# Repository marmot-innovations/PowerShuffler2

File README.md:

# PowerShuffler2
Summary: PowerShuffler2 is an update and modification of PowerShuffler1 to handle dual battery charging by intelligently multiplexing between two outputs.

Theory of operation: In a battery stack with 99 lithium-ion cells in series, there might be more than 1 weak cells that limit the usability of the entire battery pack. Let's assume the 99 li-ion cells are arranged in groups of 9 and there are certain groups that contain cells which are stronger than others. PowerShuffler2 is a PCBA that will piggy-back on top of the existing BMS that comes with the battery pack and draw power from the stronger group in order to charge up the 1 or 2 weak cells wherever they sit in the series of 99 cells. PowerShuffler2 has built-in intelligence to select the lower of the two output cell voltages and to prevent over-discharging the stronger group by measuring the voltage of the weakest cell as it rises, and comparing it to 1/9th of the stronger group's total voltage as it falls to within a certain threshold. Pre-programmed hysteresis and voltage-read-before-charging prevents excessive start-stop charging as the cells are put through normal usage during the time when the existing BMS kicks in. Although intrusive, PowerShuffler2 is meant to be a diagnostics tool to verify and characterize weak cells within a battery stack on top of a pre-existing BMS. It does not replace the need for servicing the battery pack or using a better BMS down the road. PowerShuffler2 has no wired or wireless communication, which is not accessible anyway if piggy-backed within a battery pack enclosure.

Included in this project are:
1. Firmware for client MCU
2. PCB design for PCBA

Not included in this project is:
1. Firmware for master MCU (see PowerShuffler1 project)

Read the individual README for further details. Pictures will be added later to provide instructions for programming and installation, as well as board modifications where needed. Test data will be provided eventually.

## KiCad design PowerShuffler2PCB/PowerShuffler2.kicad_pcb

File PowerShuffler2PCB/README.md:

## PowerShuffler 2.0 PCB design schematic, layout, Gerbers, and BOM  
KiCAD 5.0.0 for PCB design  
Microsoft Excel web for BOM  
No 3D model  
No XY pick and place Centroid  
No ODB++  
No footprint library  
No schematic library

Design bugs and comments:  
1. To program master MCU, remove R6 and C7 first, then replace them once programming is completed. These components will put too much load on ISP TPI programmer.
2. To program client MCU, remove C24 and R22 first, then replace them once completed. These components will put too much load on ISP TPI programmer.
3. J2 and J4 do not need soldered headers for programming. Just shove a 5-pin 0.1" straight strip header into it to establish electrical contact. Look up "sneaky footprints PCB" on the web.
4. Mounting holes are for 4-40 screws and stand-offs.
5. Peak 82% efficiency during max charge rate as measured.
6. Less than 0.5mA current draw from input when idle, not charging.
7. There is no D2 LED, only D1 and D3.

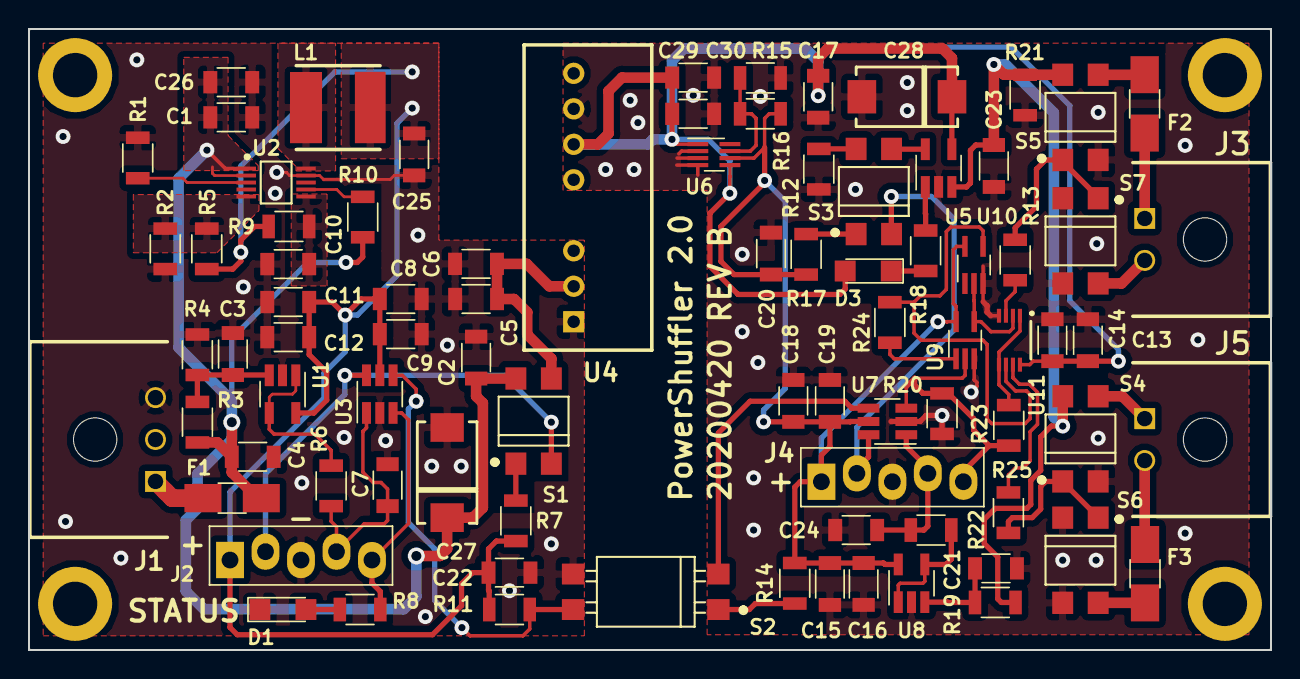
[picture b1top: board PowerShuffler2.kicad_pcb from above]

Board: 4 copper layers, 88.9 x 44.5 mm, 88 parts (0 on the bottom side), 49 nets.

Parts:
C1, C3, C5, C7, C8, C11, C13, C15, C18, C21, C22, C24, C29: 1u; C_1206
C2, C6, C9, C12, C14, C16, C19, C26, C30: 0.1u; C_1206
C4, C20, C25: 10u; C_1206
C10: 0.22u; C_1206
C17, C23: 4.7u; C_1206
C27, C28: 15u; 2917
D1, D3: LED; LED_1206
F1, F2, F3: Fuse; Fuse_SMD1206_HandSoldering
J1: Conn_01x03; Molex_Microfit3_Header_3pin_Angled_43650
J2, J4: Conn_01x05; Staggered_ICSP_5x2.54mm_Straight
J3, J5: Conn_01x02; Molex_Microfit3_Header_2pin_Angled_43650
L1: 680u; SMD_Inductor_Shielded_6x6mm
MNT1, MNT2, MNT3, MNT4: MountingHole; 3mm_hole
R1, R10, R21, R24: 191k; R_1206
R2: 49.9k; R_1206
R3: 210k; R_1206
R4: 19.1k; R_1206
R5: 158k; R_1206
R6, R13, R19, R22, R25: 390; R_1206
R7: 470; R_1206
R8, R11, R12, R18: 2k; R_1206
R9: 22.1; R_1206
R14, R17: 820; R_1206
R15: 200k; R_1206
R16, R23: 1.33M; R_1206
R20: 5.6k; R_1206
S1, S3, S4, S5, S6, S7: SSR4; SMD4_SSR_CPC1002N
S2: OPTOSOLO; SMD4_TL241AF-SSR_0.1_12x5mm
U1, U8: MCP6401; SOT-23-5_HandSoldering
U2: SWITCHDCDCLOPOW; 10-μMAX_3x3mm
U3, U7: ATTINY; SOT-23-6_Handsoldering
U4: SPBW03G
U5: MCP73831; SOT-23-5_HandSoldering
U6: LT3009; SC-70-8_Handsoldering
U9: 74AUC1G79; SOT-353_SC-70-5_Handsoldering
U10: 74AHC1G14; SOT-353_SC-70-5_Handsoldering
U11: SN74LVC2G08; VSSOP-8

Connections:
+3.3VA: C15.1, C16.1, C18.1, C19.1, C20.1, J4.1, R14.1, R16.1, R17.1, U6.6, U7.5, U8.5, U9.5, U10.5
+3V3: C8.1, C9.1, C11.1, C12.1, C22.1, C25.1, J2.1, L1.2, R5.1, R7.2, R9.1, R11.1, U1.5, U3.5
+5VA: C13.1, C14.1, C17.1, C28.1, C29.1, C30.1, D3.2, U4.6, U5.4, U6.1, U6.5, U11.8
+36V: C1.1, C2.1, C4.1, C26.1, C27.1, F1.1, R3.1, R10.2, S1.4, U2.1, U2.2
/36VSWITCH: C5.1, C6.1, S1.3, U4.2
/OUT1: R13.1, U11.3
/OUT2: R25.1, U11.7
/PB0_1: C7.1, J2.4, R6.1, U3.1
/PB0_2: C24.1, J4.4, R22.2, U7.1
/PB1_1: J2.5, R8.1, U3.3
/PB1_2: J4.5, R20.1, R23.2, U7.3, U9.2
/PB2_1: R11.2, S2.4, U3.4
/PB2_2: S2.2, U7.4
/PB3_1: J2.2, S1.2, U3.6
/PB3_2: J4.2, S3.2, U7.6
/VBATT: C23.1, R19.2, R21.1, S4.4, S5.4, U5.3
/VSUBSHEET: C3.1, R3.2, R4.1, U1.3
GND: C13.2, C14.2, C15.2, C16.2, C17.2, C18.2, C19.2, C20.2, C21.2, C23.2, C24.2, C28.2, C29.2, C30.2, J4.3, R12.1, R15.1, R20.2, R21.2, S4.2, S5.2, S6.2, S6.3, S7.2, S7.3, U4.7, U5.2, U6.2, U6.3, U6.4, U7.2, U8.2, U9.3, U10.3, U11.4
GNDS: C1.2, C2.2, C3.2, C4.2, C5.2, C6.2, C7.2, C8.2, C9.2, C10.2, C11.2, C12.2, C22.2, C25.2, C26.2, C27.2, D1.1, J1.3, J2.3, R1.2, R2.1, R4.2, S2.3, U1.2, U2.9, U3.2, U4.1
unnamed: C10.1, R9.2, U2.6
unnamed: C21.1, R19.1, U8.3
unnamed: D1.2, R8.2
unnamed: D3.1, R18.2
unnamed: F1.2, J1.1
unnamed: F2.1, J3.1
unnamed: F2.2, S5.3
unnamed: F3.1, J5.2
unnamed: F3.2, S6.4
unnamed: J3.2, S7.4
unnamed: J5.1, S4.3
unnamed: L1.1, U2.10
unnamed: R1.1, U2.3
unnamed: R2.2, R5.2, U2.5
unnamed: R6.2, U1.1, U1.4
unnamed: R7.1, S1.1
unnamed: R10.1, U2.7
unnamed: R12.2, S3.4
unnamed: R13.2, S5.1, S7.1
unnamed: R14.2, S2.1
unnamed: R15.2, R16.2, U6.7
unnamed: R17.2, S3.1
unnamed: R18.1, U5.1
unnamed: R22.1, U8.1, U8.4
unnamed: R23.1, U11.1, U11.5
unnamed: R24.1, U10.4, U11.6
unnamed: R24.2, U9.1
unnamed: R25.2, S4.1, S6.1
unnamed: S3.3, U5.5
unnamed: U9.4, U10.2, U11.2

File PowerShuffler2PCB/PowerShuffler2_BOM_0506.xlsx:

ref | quantity | qty x 3 | value | Mouser P/N | Manufacturer P/N | description | footprint
C12, C14, C16, C19, C2, C26, C30, C6, C9 | 9 | 27 | 0.1u | 791-1206B104K101CT | 1206B104K101CT | Unpolarized capacitor | Capacitors_SMD:C_1206
C10 | 1 | 3 | 0.22u |  | CL31B224KBFNNNE | Unpolarized capacitor | Capacitors_SMD:C_1206
R16, R23 | 2 | 6 | 1.33M | 667-ERJ-8ENF1334V | ERJ-8ENF1334V | Resistor 1% | Resistors_SMD:R_1206
C20, C25 | 2 | 6 | 10u | 963-LMK316B7106KL-T | LMK316B7106KL-T | Unpolarized capacitor 10V | Capacitors_SMD:C_1206
C4 | 1 | 3 | 10u |  | CL31B106KBHNNNE | Unpolarized capacitor 50V | Capacitors_SMD:C_1206
R5 | 1 | 3 | 158k |  | RMCF1206FT158K | Resistor 1% | Resistors_SMD:R_1206
C1, C3, C5 | 3 | 9 | 1u |  | CL31B105KCHNNNE | Unpolarized capacitor 100V | Capacitors_SMD:C_1206
C11, C13, C15, C18, C21, C22, C24, C29, C7, C8 | 10 | 30 | 1u | 791-MT31B105K500CT | MT31B105K500CT | Unpolarized capacitor 50V | Capacitors_SMD:C_1206
C17, C23 | 2 | 6 | 4.7u | 80-C1206C475K4P7210 | C1206C475K4PAC7210 | Unpolarized capacitor | Capacitors_SMD:C_1206
C27, C28 | 2 | 6 | 15u | 80-T491X226K50ATAUTO | T491X226K050ATAUTO | Unpolarized capacitor 50V | BMB:2917
R1, R10, R24 | 3 | 9 | 191k | 667-ERJ-8ENF1913V | ERJ-8ENF1913V | Resistor 1% | Resistors_SMD:R_1206
R11, R12, R18, R8 | 4 | 12 | 2k | 652-CR1206FX-2001ELF | CR1206-FX-2001ELF | Resistor 1% | Resistors_SMD:R_1206
R13, R19, R22, R25, R6 | 5 | 15 | 390 | 652-CR1206FX-3900ELF | CR1206-FX-3900ELF | Resistor 1% | Resistors_SMD:R_1206
R14, R17 | 2 | 6 | 820 | 660-RK73B2BTTE821J | RK73B2BTTE821J | Resistor 5% | Resistors_SMD:R_1206
R15 | 1 | 3 | 200k | 667-ERJ-8ENF2003V | ERJ-8ENF2003V | Resistor 1% | Resistors_SMD:R_1206
R3 | 1 | 3 | 210k |  | ERA-8AEB2103V | Resistor 0.1% | Resistors_SMD:R_1206
R4 | 1 | 3 | 18.7k |  | ERA-8AEB1872V | Resistor 0.1% | Resistors_SMD:R_1206
R7 | 1 | 3 | 470 |  | RMCF1206JT470R | Resistor 5% | Resistors_SMD:R_1206
R2 | 1 | 3 | 49.9k |  | RMCF1206FT49K9 | Resistor 1% | Resistors_SMD:R_1206
R20, R21 | 2 | 6 | 5.6k | 652-CR1206FX-5601ELF | CR1206-FX-5601ELF | Resistor 1% | Resistors_SMD:R_1206
R9 | 1 | 3 | 22.1 |  | RMCF1206FT22R1 | Resistor 1% | Resistors_SMD:R_1206
L1 | 1 | 3 | 680u | 810-VLS6045EX-681M | VLS6045EX-681M | Inductor | BMB:SMD_Inductor_Shielded_6x6mm
U1, U8 | 2 | 6 | MCP6401 | 579-MCP6401T-H/OTVAO | MCP6401T-H/OTVAO | Precision Micropower, Low Noise CMOS, Rail-to-Rail Input/Output Operational Amp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 | TO_SOT_Packages_SMD:SOT-23-5_HandSoldering
U10 | 1 | 3 | 74AHC1G14 | 771-74AHC1G14GW-G | 74AHC1G14GW,125 | Single Schmitt NOT Gate, Low-Voltage CMOS | TO_SOT_Packages_SMD:SOT-353_SC-70-5_Handsoldering
U11 | 1 | 3 | SN74LVC2G08 | 595-SN74LVC2G08DCUR | SN74LVC2G08DCUR |  | BMB:VSSOP-8
U2 | 1 | 3 | SWITCHDCDCLOPOW | 700-MAX17550AUB+ | MAX17550AUB+ |  | BMB:10-μMAX_3x3mm
U3, U7 | 2 | 6 | ATTINY | 556-ATTINY10-TSHR | ATTINY10-TSHR |  | TO_SOT_Packages_SMD:SOT-23-6_Handsoldering
U4 | 1 | 3 | SPBW03G | 709-SPBW03G-05 | SPBW03G-05 |  | BMB:SPBW03G
U5 | 1 | 3 | MCP73831 | 579-MCP73831T-3ACIOT | MCP73831T-3ACI/OT | 4.35V Li-Ion 500mA charger SOT-23-5 | TO_SOT_Packages_SMD:SOT-23-5_HandSoldering
U6 | 1 | 3 | LT3009 | 584-LT3009ESC8TRMPBF | LT3009ESC8#TRMPBF |  | TO_SOT_Packages_SMD:SC-70-8_Handsoldering
U9 | 1 | 3 | 74AUC1G79 | 771-74AHC1G79GW-G | 74AHC1G79GW,125 | Single D Flip-Flop, Low-Voltage CMOS | TO_SOT_Packages_SMD:SOT-353_SC-70-5_Handsoldering
J3, J5 | 2 | 6 | Conn_01x02 | 538-43650-0200 | 43650-0200 |  | BMB:Molex_Microfit3_Header_2pin_Angled_43650
J1 | 1 | 3 | Conn_01x03 | 538-43650-0301 | 43650-0301 |  | BMB:Molex_Microfit3_Header_3pin_Angled_43650
J2, J4 | 2 | 6 | Conn_01x05 | N/A | N/A | staggered 0.1" spaced hole programming port | BMB:Staggered_ICSP_5x2.54mm_Straight
F1 | 1 | 3 | Fuse | 576-0468002.NRHF | 0468002.NR | Surface Mount Fuses 1206 SLO-BLO 2A SLIMLINE HALIDE FREE | Fuse_Holders_and_Fuses:Fuse_SMD1206_HandSoldering
F2, F3 | 2 | 6 | Fuse | 650-1206SFP200F/63-2 | 1206SFP200F/63-2 | Surface Mount Fuses VERY FAST GLASS CER 63V 2A SZ 1206 | Fuse_Holders_and_Fuses:Fuse_SMD1206_HandSoldering
D1 | 1 | 3 | LED | 710-150120GS75000 | 150120GS75000 | Green LED 1206 | LEDs:LED_1206
D3 | 1 | 3 | LED | 710-150120RS75000 | 150120RS75000 | Red LED 1206 | LEDs:LED_1206
S1 | 1 | 3 | SSR4 | 849-CPC1002N | CPC1002N | Solid State Relays - PCB Mount 1-Form-A 60V 700mA Solid State Relay MOSFET w/ i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 | BMB:SMD4_SSR_CPC1002N
S2 | 1 | 3 | OPTOSOLO | 859-LTV-816S | LTV-816S | Transistor Output Optocouplers Optocoupler Phototrans PDIP-4 Gull Wing | BMB:SMD4_TL241AF-SSR_0.1_12x5mm
S3 | 1 | 3 | SSR4 | 782-VO1400AEFTR | VO1400AEFTR | Solid State Relays - PCB Mount Normally Open Form 1A SOP-4 100mA load very low 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 | BMB:SMD4_SSR_CPC1002N
S4, S5, S6, S7 | 4 | 12 | SSR4 | 876-SMP-1A47-4PT | SMP-1A47-4PT | Solid State Relays - PCB Mount 1 Form A 80V 1.25A SOP-4 that does not have MOSF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

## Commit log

2020-05-31 Update README with verbose description
2020-05-31 Create README and new folder
2020-05-31 Add PCB design files and BOM
2020-05-31 to be deleted
2020-05-31 Add PCB Gerber and drill files
2020-05-31 formatting
2020-05-31 Add Atmel Studio project file
2020-05-31 Add AtmelStudio source files, client MCU fw
    PowerShuffler2
2020-05-31 Update README to locate master MCU fw
    master MCU fw is in PowerShuffler1
